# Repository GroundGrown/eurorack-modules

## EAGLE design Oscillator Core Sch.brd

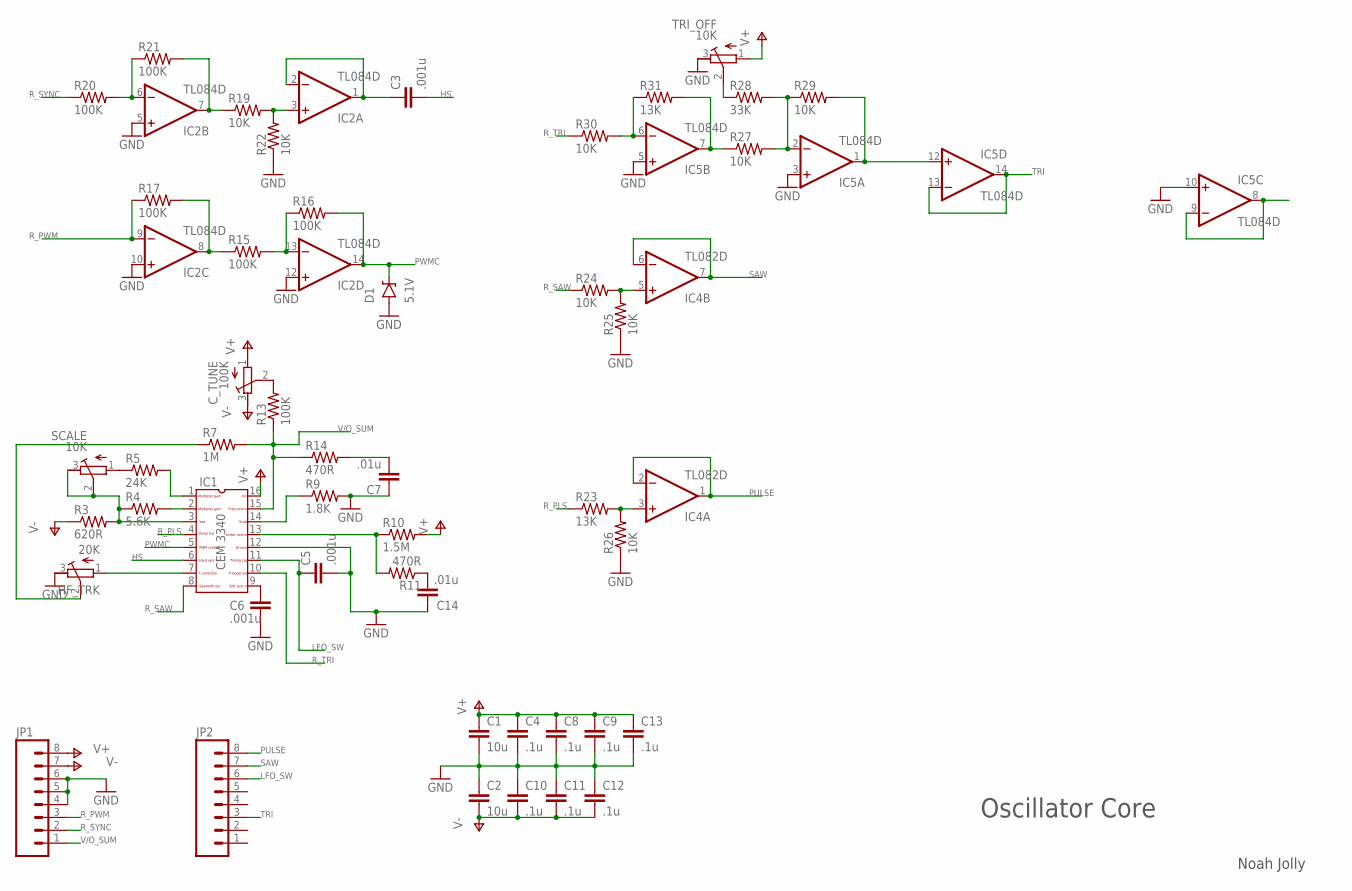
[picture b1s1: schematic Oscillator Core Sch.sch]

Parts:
C1, C2: 10u; 1206
C3, C6: .001u; 0805
C4, C8, C9, C10, C11, C12, C13: .1u; 0805
C5: .001u; CAP-PTH-5MM
C7, C14: .01u; 0805
C_TUNE: 100K; RTRIM3296Y
D1: 5.1V; SOD-123
HF_TRK: 20K; RTRIM3296Y
IC1: CEM3340; DIL16
IC2, IC5: TL084D; SO14
IC4: TL082D; SO08
JP1, JP2: M08; 1X08_ROUND
R3: 620R; 0805@1
R4: 5.6K; 0805@1
R5: 24K; 0805@1
R7: 1M; 0805@1
R9: 1.8K; 0805@1
R10: 1.5M; 0805@1
R11, R14: 470R; 0805@1
R13, R15, R16, R17, R20, R21: 100K; 0805@1
R19, R22, R24, R25, R26, R27, R29, R30: 10K; 0805@1
R23, R31: 13K; 0805@1
R28: 33K; 0805@1
SCALE: 10K; RTRIM3296Y
TRI_OFF: 10K; RTRIM3296Y

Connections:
GND: C1.2, C2.1, C4.2, C5.2, C6.2, C7.1, C8.2, C9.2, C10.1, C11.1, C12.1, C13.2, C14.1, D1.A, HF_TRK.3 (E), IC1.12, IC2.5 (+IN), IC2.10 (+IN), IC2.12 (+IN), IC5.3 (+IN), IC5.5 (+IN), IC5.10 (+IN), JP1.4, JP1.5, JP1.6, R9.2, R22.1, R25.1, R26.1, TRI_OFF.3 (E)
HS: C3.2, IC1.6
LFO_SW: C5.1, IC1.11, JP2.6
unnamed: R5.1, SCALE.1 (A)
unnamed: IC1.3, R3.2, R4.1, SCALE.2 (S), SCALE.3 (E)
unnamed: IC1.2, R4.2
unnamed: IC1.1, R5.2
unnamed: HF_TRK.2 (S), R7.1
unnamed: HF_TRK.1 (A), IC1.7
unnamed: C_TUNE.2 (S), R13.2
unnamed: IC1.14, R9.1
unnamed: IC1.13, R10.1, R11.2
unnamed: IC2.8 (OUT), R15.1, R17.2
unnamed: C6.1, IC1.9
unnamed: IC2.13 (-IN), R15.2, R16.1
unnamed: C7.2, R14.2
unnamed: IC4.5 (+IN), R24.2, R25.2
unnamed: IC5.8 (OUT), IC5.9 (-IN)
unnamed: C14.2, R11.1
unnamed: IC2.3 (+IN), R19.2, R22.2
unnamed: IC2.6 (-IN), R20.2, R21.1
unnamed: IC2.7 (OUT), R19.1, R21.2
unnamed: C3.1, IC2.1 (OUT), IC2.2 (-IN)
unnamed: IC4.3 (+IN), R23.2, R26.2
unnamed: IC5.6 (-IN), R30.2, R31.1
unnamed: IC5.7 (OUT), R27.1, R31.2
unnamed: IC5.2 (-IN), R27.2, R28.2, R29.1
unnamed: IC5.1 (OUT), IC5.12 (+IN), R29.2
unnamed: R28.1, TRI_OFF.2 (S)
PULSE: IC4.1 (OUT), IC4.2 (-IN), JP2.8
PWMC: D1.C, IC1.5, IC2.14 (OUT), R16.2
R_PLS: IC1.4, R23.1
R_PWM: IC2.9 (-IN), JP1.3, R17.1
R_SAW: IC1.8, R24.1
R_SYNC: JP1.2, R20.1
R_TRI: IC1.10, R30.1
SAW: IC4.6 (-IN), IC4.7 (OUT), JP2.7
TRI: IC5.13 (-IN), IC5.14 (OUT), JP2.3
V+: C1.1, C4.1, C8.1, C9.1, C13.1, C_TUNE.1 (A), IC1.16, IC2.4 (V+), IC4.8 (V+), IC5.4 (V+), JP1.8, R10.2, TRI_OFF.1 (A)
V-: C2.2, C10.2, C11.2, C12.2, C_TUNE.3 (E), IC2.11 (V-), IC4.4 (V-), IC5.11 (V-), JP1.7, R3.1
V/O_SUM: IC1.15, JP1.1, R7.2, R13.1, R14.1

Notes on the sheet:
Oscillator Core
Noah Jolly

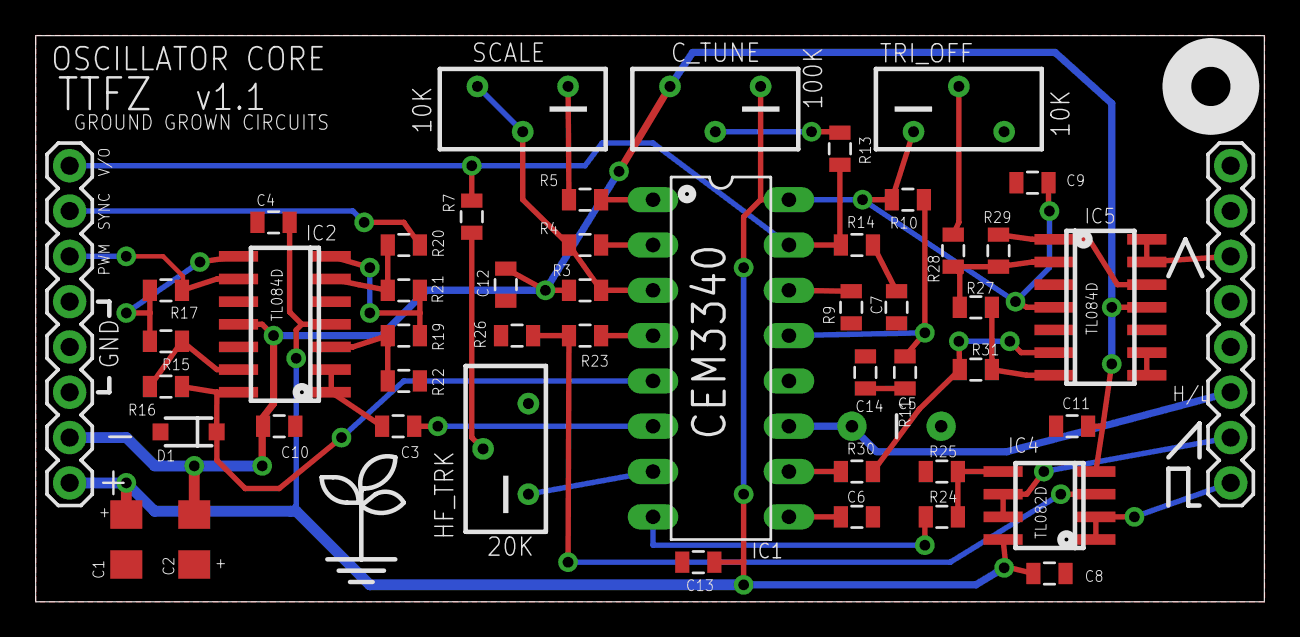
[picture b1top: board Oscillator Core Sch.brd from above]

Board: 2 copper layers, 68.9 x 31.7 mm, 50 parts (0 on the bottom side), 41 nets.

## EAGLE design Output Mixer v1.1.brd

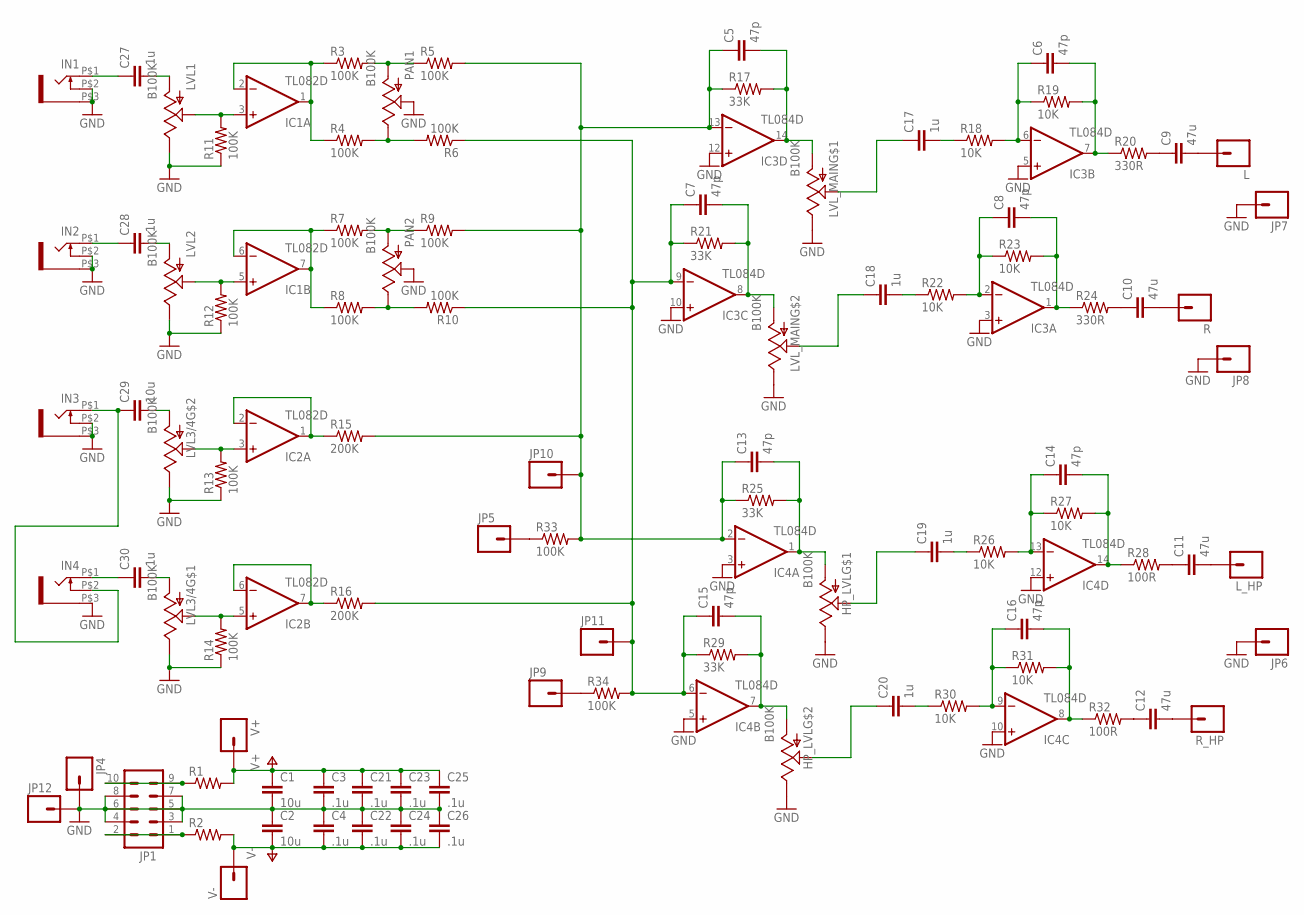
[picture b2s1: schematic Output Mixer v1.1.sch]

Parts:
C1, C2, C29: 10u; 1206
C3, C4, C21, C22, C23, C24, C25, C26: .1u; 0805
C5, C6, C7, C8, C13, C14, C15, C16: 47p; 0805
C9, C10, C11, C12: 47u; 1206
C17, C18, C19, C20: 1u; 0805
C27, C28, C30: .1u; 1206
HP_LVL: B100K; ALPS/ALPHA_POT_DUAL
IC1, IC2: TL082D; SO08
IC3, IC4: TL084D; SO14
IN1, IN2, IN3, IN4: WQP-PJ301M-12_JACK
JP1: M05X2PTH; AVR_ICSP
JP4, JP5, JP6, JP7, JP8, JP9, JP10, JP11, JP12: M01PTH; 1X01
L: M01PTH; 1X01
LVL1, LVL2: B100K; ALPS_POT
LVL3/4: B100K; ALPS/ALPHA_POT_DUAL
LVL_MAIN: B100K; ALPS/ALPHA_POT_DUAL
L_HP: M01PTH; 1X01
PAN1, PAN2: B100K; ALPS_POT
R: M01PTH; 1X01
R1, R2: RESISTOR0805-RES; 0805
R3, R4, R5, R6, R7, R8, R9, R10, R11, R12, R13, R14, R33, R34: 100K; 0805
R15, R16: 200K; 0805
R17, R21, R25, R29: 33K; 0805
R18, R19, R22, R23, R26, R27, R30, R31: 10K; 0805
R20, R24: 330R; 0805
R28, R32: 100R; 0805
R_HP: M01PTH; 1X01
V+: M01PTH; 1X01
V-: M01PTH; 1X01

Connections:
GND: C1.2, C2.1, C3.2, C4.1, C21.2, C22.1, C23.2, C24.1, C25.2, C26.1, HP_LVL.P$1 (E), HP_LVL.P$4 (E), IC3.3 (+IN), IC3.5 (+IN), IC3.10 (+IN), IC3.12 (+IN), IC4.3 (+IN), IC4.5 (+IN), IC4.10 (+IN), IC4.12 (+IN), IN1.P$2 (3), IN1.P$3 (1), IN2.P$2 (3), IN2.P$3 (1), IN3.P$2 (3), IN3.P$3 (1), IN4.P$3 (1), JP1.3, JP1.4, JP1.5, JP1.6, JP1.7, JP1.8, JP4.1, JP6.1, JP7.1, JP8.1, JP12.1, LVL1.P$1 (E), LVL2.P$1 (E), LVL3/4.P$1 (E), LVL3/4.P$4 (E), LVL_MAIN.P$1 (E), LVL_MAIN.P$4 (E), PAN1.P$2 (S), PAN2.P$2 (S), R11.1, R12.1, R13.1, R14.1
unnamed: JP1.9, JP1.10, R1.1
unnamed: JP1.1, JP1.2, R2.1
unnamed: JP5.1, R33.1
unnamed: JP9.1, R34.1
unnamed: C30.1, IN4.P$1 (2)
unnamed: C30.2, LVL3/4.P$3 (A)
unnamed: IC1.3 (+IN), LVL1.P$2 (S), R11.2
unnamed: IC1.5 (+IN), LVL2.P$2 (S), R12.2
unnamed: IC2.6 (-IN), IC2.7 (OUT), R16.1
unnamed: IC1.1 (OUT), IC1.2 (-IN), R3.1, R4.1
unnamed: IC1.6 (-IN), IC1.7 (OUT), R7.1, R8.1
unnamed: PAN1.P$3 (A), R3.2, R5.1
unnamed: PAN1.P$1 (E), R4.2, R6.2
unnamed: PAN2.P$3 (A), R7.2, R9.1
unnamed: PAN2.P$1 (E), R8.2, R10.2
unnamed: C29.1, IN3.P$1 (2), IN4.P$2 (3)
unnamed: IC2.3 (+IN), LVL3/4.P$5 (S), R13.2
unnamed: C9.1, R20.2
unnamed: IC2.5 (+IN), LVL3/4.P$2 (S), R14.2
unnamed: IC2.1 (OUT), IC2.2 (-IN), R15.1
unnamed: C10.1, R24.2
unnamed: C7.2, IC3.8 (OUT), LVL_MAIN.P$6 (A), R21.2
unnamed: C8.1, IC3.2 (-IN), R22.2, R23.1
unnamed: C8.2, IC3.1 (OUT), R23.2, R24.1
unnamed: C11.1, R28.2
unnamed: C5.2, IC3.14 (OUT), LVL_MAIN.P$3 (A), R17.2
unnamed: C6.1, IC3.6 (-IN), R18.2, R19.1
unnamed: C6.2, IC3.7 (OUT), R19.2, R20.1
unnamed: C12.1, R32.2
unnamed: C12.2, R_HP.1
unnamed: C11.2, L_HP.1
unnamed: C9.2, L.1
unnamed: C19.1, HP_LVL.P$2 (S)
unnamed: C19.2, R26.1
unnamed: C7.1, C15.1, IC3.9 (-IN), IC4.6 (-IN), JP11.1, R6.1, R10.1, R16.2, R21.1, R29.1, R34.2
unnamed: C15.2, HP_LVL.P$6 (A), IC4.7 (OUT), R29.2
unnamed: C16.1, IC4.9 (-IN), R30.2, R31.1
unnamed: C16.2, IC4.8 (OUT), R31.2, R32.1
unnamed: C5.1, C13.1, IC3.13 (-IN), IC4.2 (-IN), JP10.1, R5.2, R9.2, R15.2, R17.1, R25.1, R33.2
unnamed: C13.2, HP_LVL.P$3 (A), IC4.1 (OUT), R25.2
unnamed: C14.1, IC4.13 (-IN), R26.2, R27.1
unnamed: C14.2, IC4.14 (OUT), R27.2, R28.1
unnamed: C10.2, R.1
unnamed: C20.1, HP_LVL.P$5 (S)
unnamed: C20.2, R30.1
unnamed: C29.2, LVL3/4.P$6 (A)
unnamed: C18.1, LVL_MAIN.P$5 (S)
unnamed: C28.1, IN2.P$1 (2)
unnamed: C28.2, LVL2.P$3 (A)
unnamed: C27.1, IN1.P$1 (2)
unnamed: C27.2, LVL1.P$3 (A)
unnamed: C18.2, R22.1
unnamed: C17.1, LVL_MAIN.P$2 (S)
unnamed: C17.2, R18.1
V+: C1.1, C3.1, C21.1, C23.1, C25.1, IC1.8 (V+), IC2.8 (V+), IC3.4 (V+), IC4.4 (V+), R1.2, V+.1
V-: C2.2, C4.2, C22.2, C24.2, C26.2, IC1.4 (V-), IC2.4 (V-), IC3.11 (V-), IC4.11 (V-), R2.2, V-.1

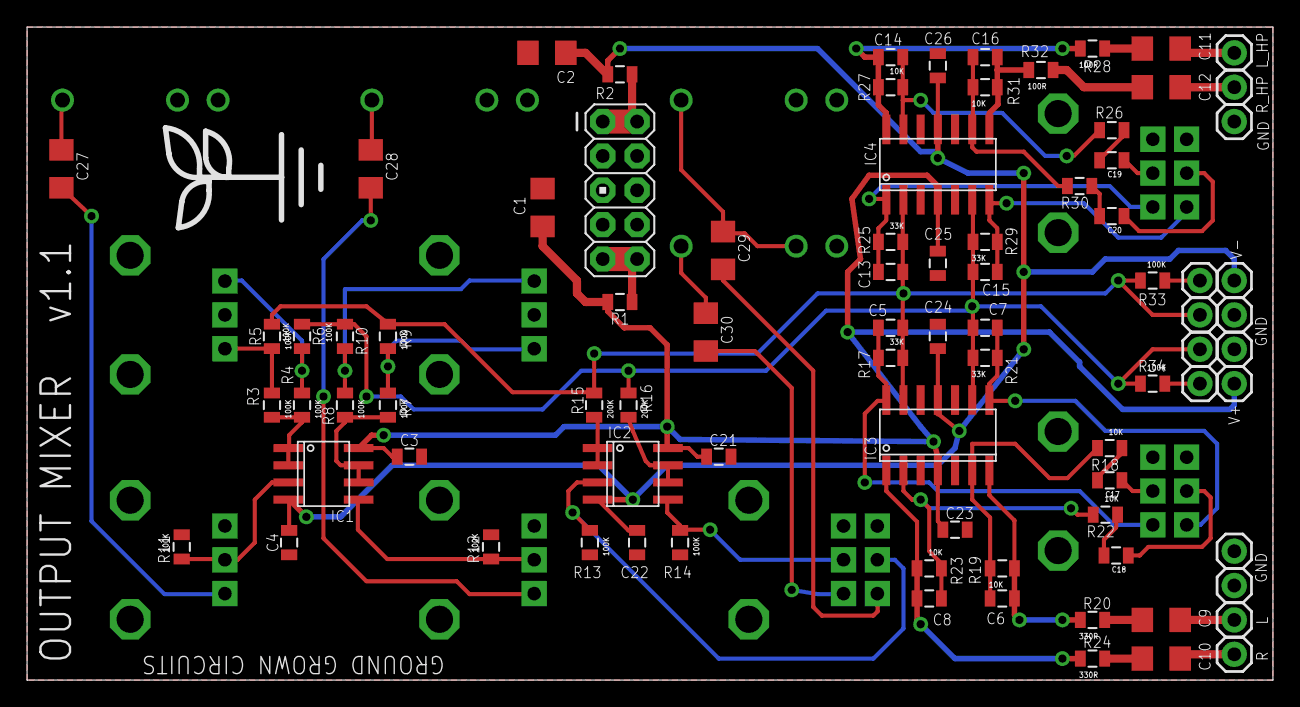
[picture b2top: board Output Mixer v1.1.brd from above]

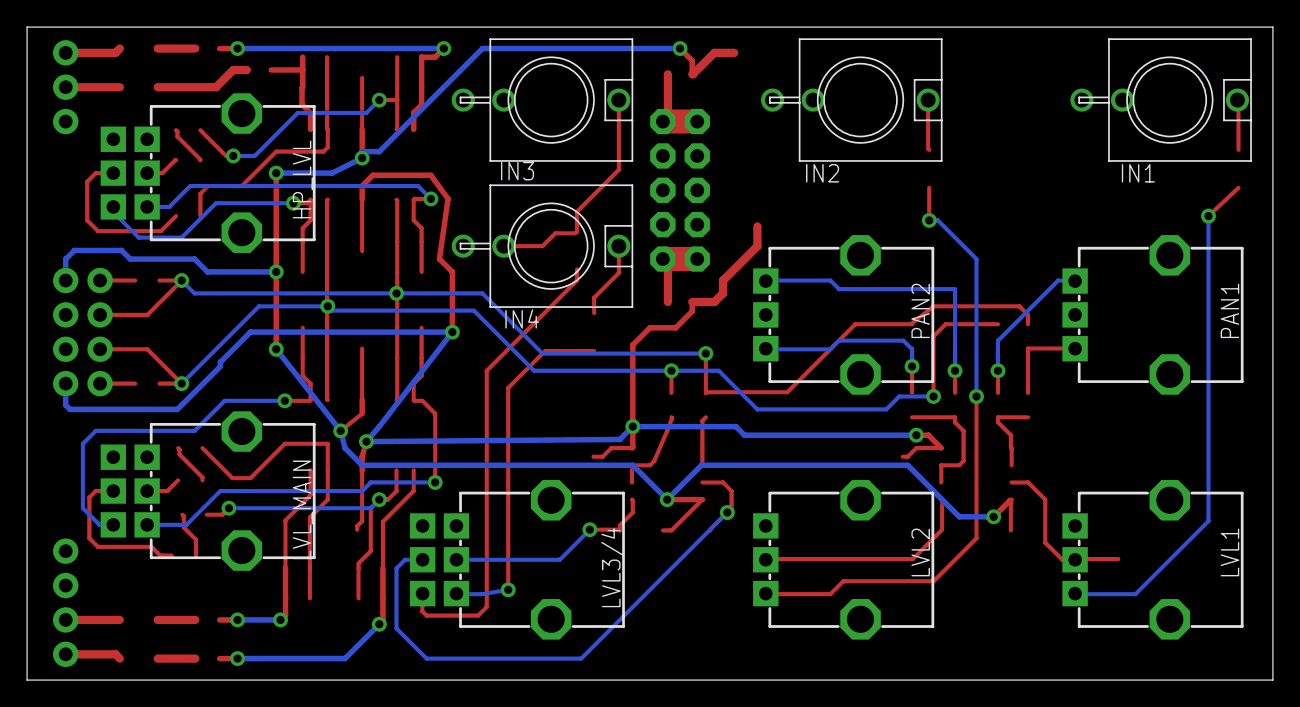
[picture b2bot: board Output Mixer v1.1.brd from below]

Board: 2 copper layers, 92.1 x 48.3 mm, 96 parts (11 on the bottom side), 57 nets.

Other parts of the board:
U$1: LOGO_MED

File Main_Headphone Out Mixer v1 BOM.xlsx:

2 | FERRITE BEAD | R1, R2
2 | 100R | R28, R32
2 | 330R | R20, R24
8 | 10K | R18, R19, R22, R23, R26, R27, R30, R31
4 | 33K | R17, R21, R25, R29
14 | 100K | R3, R4, R5, R6, R7, R8, R9, R10, R11, R12, R13, R14, R33, R34
2 | 200K | R15, R16
8 | 47p (0805) | C5, C6, C7, C8, C13, C14, C15, C16
8 | .1u (0805) | C3, C4, C21, C22, C23, C24, C25, C26
4 | .1u (1206) | C27, C28, C29, C30
2 | 10u (1206) | C1, C2
4 | 47u (1206) | C9, C10, C11, C12
2 | TL082 | IC1, IC2
2 | TL084 | IC3, IC4
1 | 2x5 pos male .1" Header | JP1
4 | B100K | LVL1, LVL2, PAN1, PAN2
3 | B100K DUAL GANG | LVL3/4, LVL_MAIN, HP_LVL
4 | WQP-PJ301M-12_JACK | IN1, IN2, IN3, IN4
2 | 1/4" MONO Jack | L_OUT, R_OUT | Switchcraft
1 | 1/4" STEREO Jack | HP_OUT | Switchcraft

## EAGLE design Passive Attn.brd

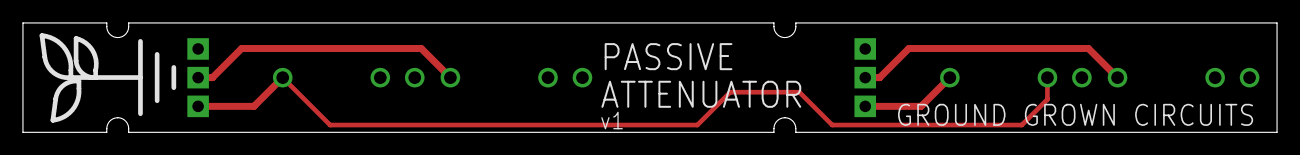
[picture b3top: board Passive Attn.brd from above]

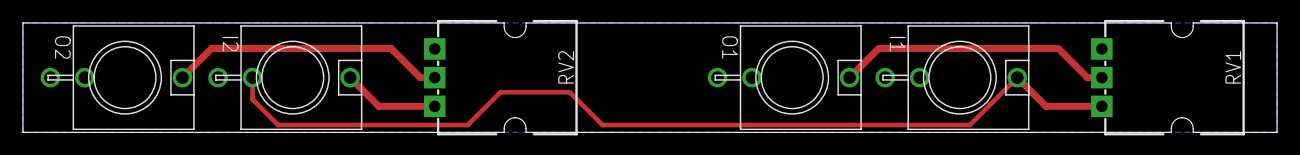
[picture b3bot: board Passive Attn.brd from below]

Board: 2 copper layers, 109.2 x 9.5 mm, 7 parts (6 on the bottom side), 5 nets.

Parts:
I1, I2: WQP-PJ301M-12_JACK
O1, O2: WQP-PJ301M-12_JACK
RV1, RV2: ALPS_POT_NO_CLIPS
U$1: LOGO_MED

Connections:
GND: I1.P$2, I1.P$3, I2.P$3, O1.P$3, O2.P$3, RV1.P$1, RV2.P$1
unnamed: O1.P$1, RV1.P$2
unnamed: I1.P$1, I2.P$2, RV1.P$3
unnamed: O2.P$1, RV2.P$2
unnamed: I2.P$1, RV2.P$3

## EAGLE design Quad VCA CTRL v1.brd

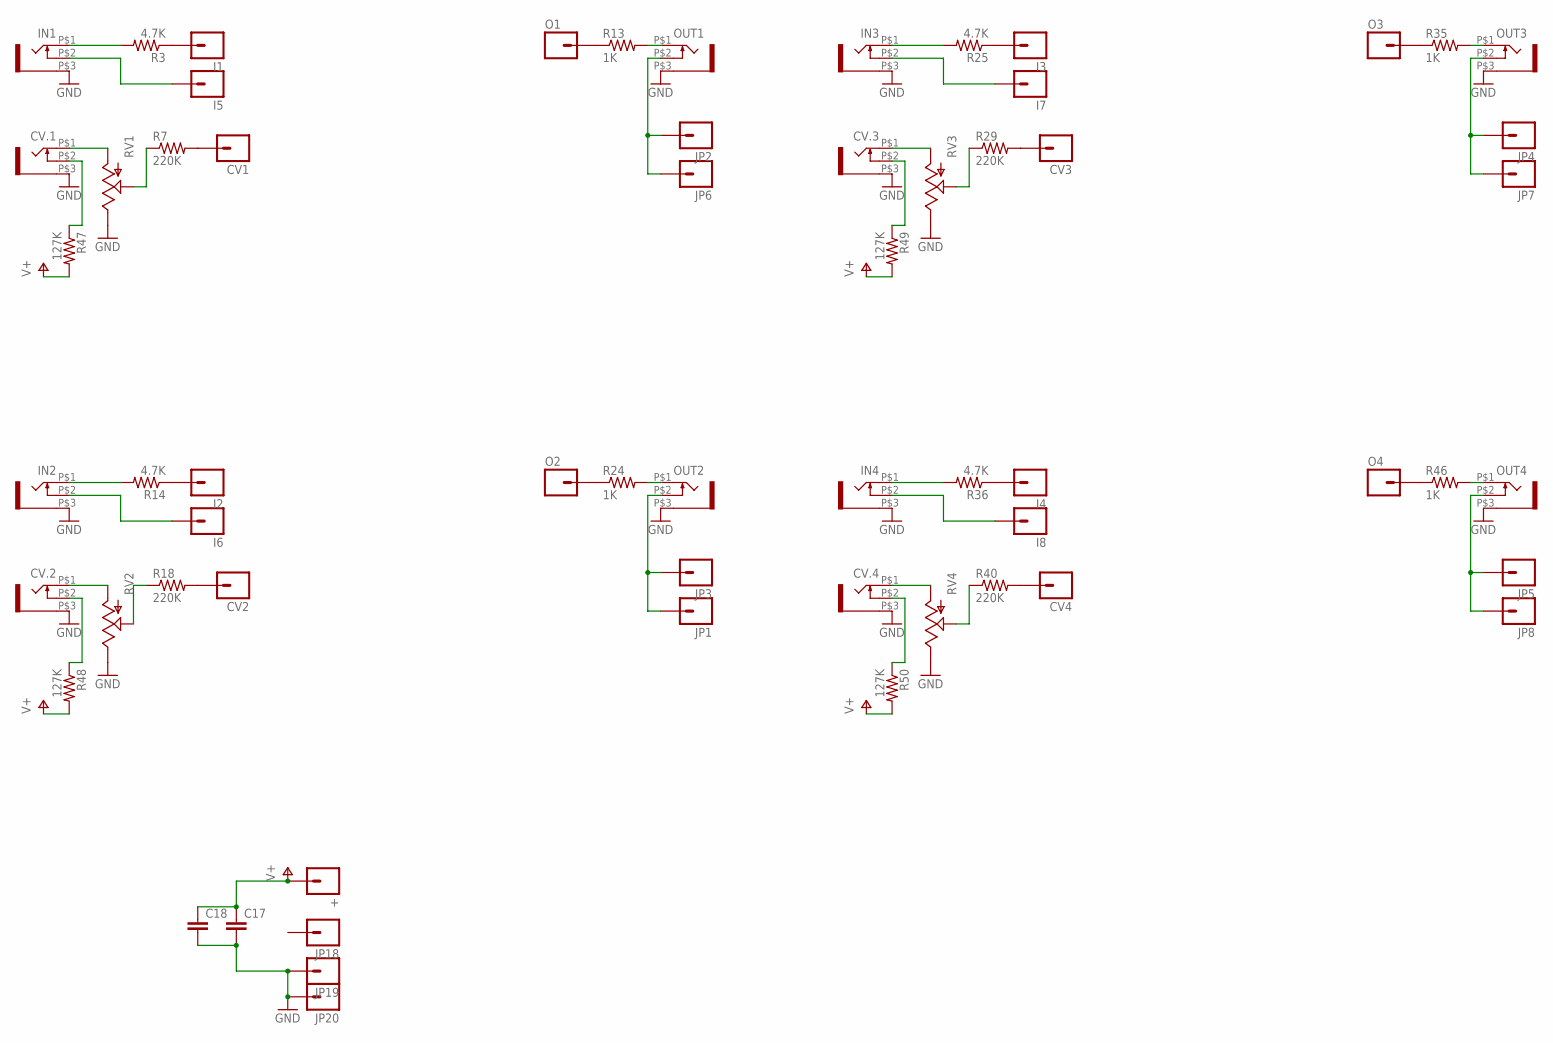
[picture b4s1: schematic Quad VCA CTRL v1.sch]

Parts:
+: M01PTH; 1X01
C17, C18: CAP0805; 0805
CV1, CV2, CV3, CV4: M01PTH; 1X01
CV.1, CV.2, CV.3, CV.4: WQP-PJ301M-12_JACK
I1, I2, I3, I4, I5, I6, I7, I8: M01PTH; 1X01
IN1, IN2, IN3, IN4: WQP-PJ301M-12_JACK
JP1, JP2, JP3, JP4, JP5, JP6, JP7, JP8, JP18, JP19, JP20: M01PTH; 1X01
O1, O2, O3, O4: M01PTH; 1X01
OUT1, OUT2, OUT3, OUT4: WQP-PJ301M-12_JACK
R3, R14, R25, R36: 4.7K; 0805
R7, R18, R29, R40: 220K; 0805
R13, R24, R35, R46: 1K; 0805
R47, R48, R49, R50: 127K; 0805
RV1, RV2, RV3, RV4: POT; ALPS_POT

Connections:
GND: C17.2, C18.2, CV.1.P$3 (1), CV.2.P$3 (1), CV.3.P$3 (1), CV.4.P$3 (1), IN1.P$3 (1), IN2.P$3 (1), IN3.P$3 (1), IN4.P$3 (1), JP19.1, JP20.1, OUT1.P$3 (1), OUT2.P$3 (1), OUT3.P$3 (1), OUT4.P$3 (1), RV1.P$1 (E), RV2.P$1 (E), RV3.P$1 (E), RV4.P$1 (E)
unnamed: CV.1.P$2 (3), R47.1
unnamed: I1.1, R3.1
unnamed: IN1.P$1 (2), R3.2
unnamed: CV1.1, R7.2
unnamed: O1.1, R13.1
unnamed: CV.2.P$1 (2), RV2.P$3 (A)
unnamed: CV.2.P$2 (3), R48.1
unnamed: CV.3.P$2 (3), R49.1
unnamed: CV.4.P$2 (3), R50.1
unnamed: JP2.1, JP6.1, OUT1.P$2 (3)
unnamed: IN2.P$1 (2), R14.2
unnamed: I2.1, R14.1
unnamed: O2.1, R24.1
unnamed: O3.1, R35.1
unnamed: O4.1, R46.1
unnamed: CV4.1, R40.2
unnamed: I4.1, R36.1
unnamed: CV3.1, R29.2
unnamed: R18.1, RV2.P$2 (S)
unnamed: CV.1.P$1 (2), RV1.P$3 (A)
unnamed: I3.1, R25.1
unnamed: CV2.1, R18.2
unnamed: I5.1, IN1.P$2 (3)
unnamed: I6.1, IN2.P$2 (3)
unnamed: OUT2.P$1 (2), R24.2
unnamed: IN3.P$1 (2), R25.2
unnamed: I7.1, IN3.P$2 (3)
unnamed: I8.1, IN4.P$2 (3)
unnamed: R7.1, RV1.P$2 (S)
unnamed: CV.3.P$1 (2), RV3.P$3 (A)
unnamed: R29.1, RV3.P$2 (S)
unnamed: CV.4.P$1 (2), RV4.P$3 (A)
unnamed: OUT1.P$1 (2), R13.2
unnamed: OUT3.P$1 (2), R35.2
unnamed: IN4.P$1 (2), R36.2
unnamed: R40.1, RV4.P$2 (S)
unnamed: JP1.1, JP3.1, OUT2.P$2 (3)
unnamed: OUT4.P$1 (2), R46.2
unnamed: JP4.1, JP7.1, OUT3.P$2 (3)
unnamed: JP5.1, JP8.1, OUT4.P$2 (3)
V+: +.1, C17.1, C18.1, R47.2, R48.2, R49.2, R50.2

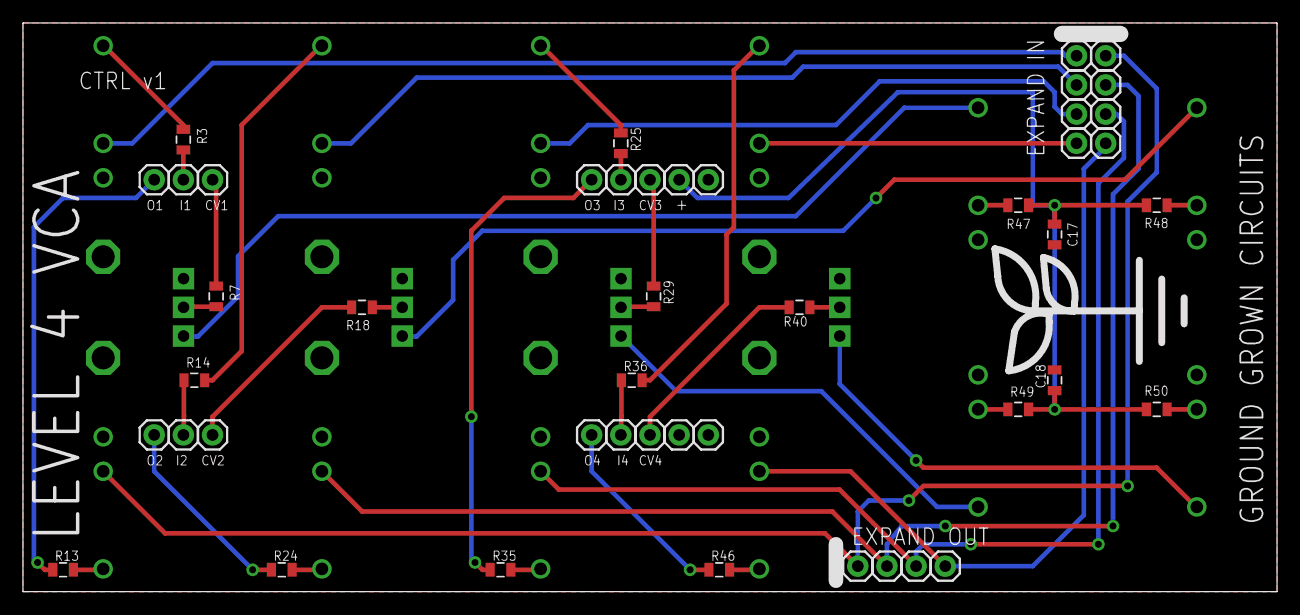
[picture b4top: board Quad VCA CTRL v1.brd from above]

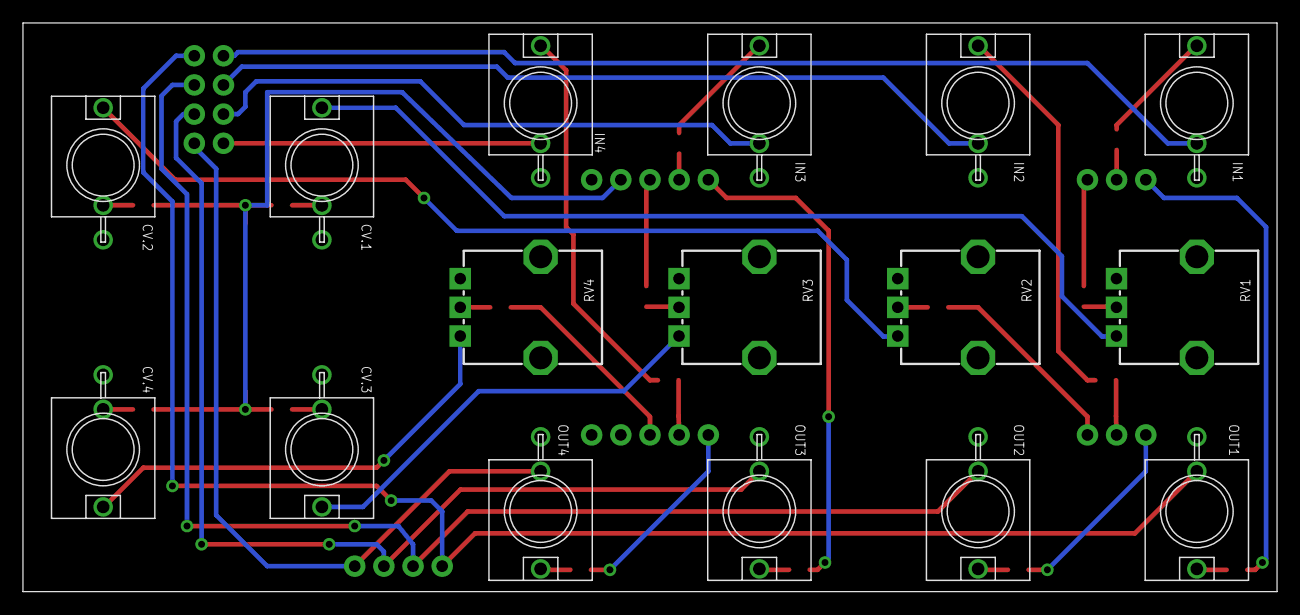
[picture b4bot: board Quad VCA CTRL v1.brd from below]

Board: 2 copper layers, 109.2 x 49.5 mm, 63 parts (16 on the bottom side), 42 nets.

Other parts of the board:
U$1: LOGO_LARGE

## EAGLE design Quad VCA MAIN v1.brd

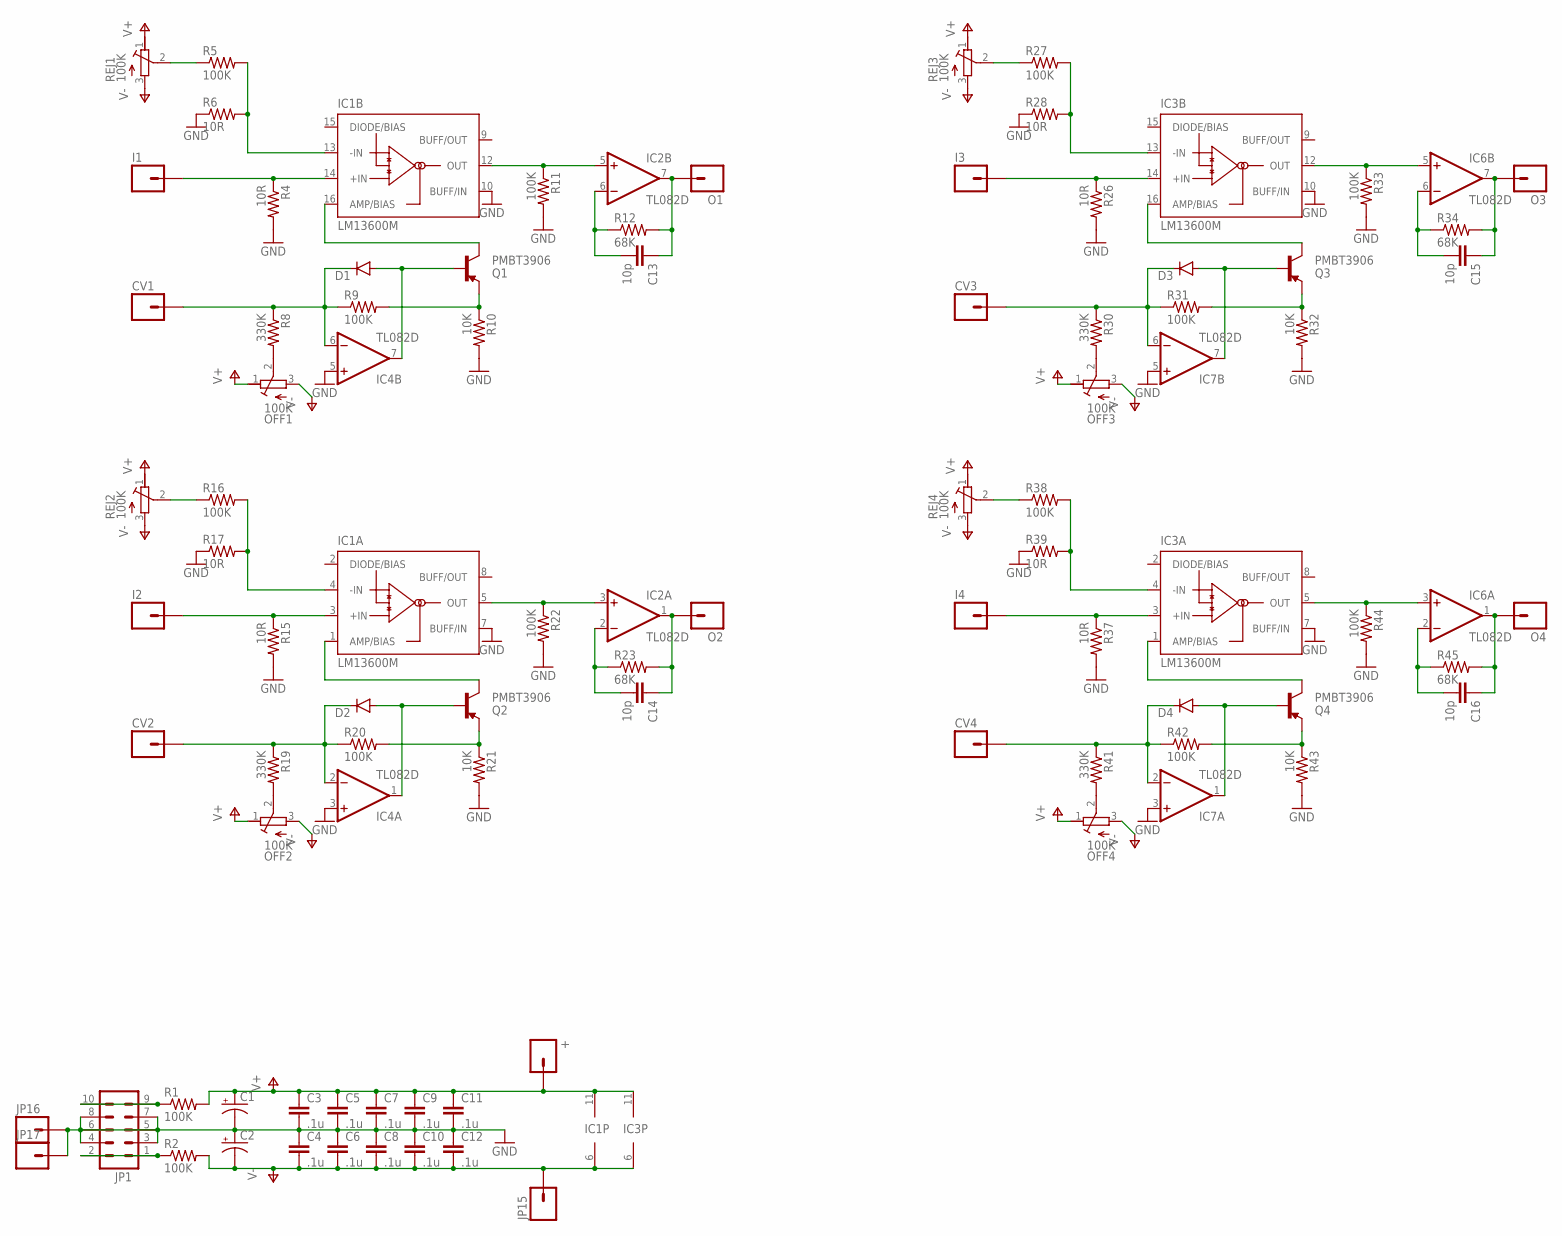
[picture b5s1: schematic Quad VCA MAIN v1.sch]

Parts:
+: M01PTH; 1X01
C1, C2: CAP_POLPTH2; CPOL-RADIAL-10UF-25V
C3, C4, C5, C6, C7, C8, C9, C10, C11, C12: .1u; 0805
C13, C14, C15, C16: 10p; 0805
CV1, CV2, CV3, CV4: M01PTH; 1X01
D1, D2, D3, D4: DIODESOD123; SOD-123
I1, I2, I3, I4: M01PTH; 1X01
IC1, IC3: LM13600M; SO16
IC2, IC4, IC6, IC7: TL082D; SO08
JP1: M05X2PTH; AVR_ICSP
JP15, JP16, JP17: M01PTH; 1X01
O1, O2, O3, O4: M01PTH; 1X01
OFF1, OFF2, OFF3, OFF4: 100K; RTRIM3314G
Q1, Q2, Q3, Q4: PMBT3906; SOT23-3
R1, R2, R5, R9, R11, R16, R20, R22, R27, R31, R33, R38, R42, R44: 100K; 0805
R4, R6, R15, R17, R26, R28, R37, R39: 10R; 0805
R8, R19, R30, R41: 330K; 0805
R10, R21, R32, R43: 10K; 0805
R12, R23, R34, R45: 68K; 0805
REJ1, REJ2, REJ3, REJ4: 100K; RTRIM3314G

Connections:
GND: C1.2 (-), C2.1 (+), C3.2, C4.1, C5.2, C6.1, C7.2, C8.1, C9.2, C10.1, C11.2, C12.1, IC1.7 (BUFF/IN), IC1.10 (BUFF/IN), IC3.7 (BUFF/IN), IC3.10 (BUFF/IN), IC4.3 (+IN), IC4.5 (+IN), IC7.3 (+IN), IC7.5 (+IN), JP1.3, JP1.4, JP1.5, JP1.6, JP1.7, JP1.8, JP16.1, JP17.1, R4.2, R6.1, R10.2, R11.2, R15.2, R17.1, R21.2, R22.2, R26.2, R28.1, R32.2, R33.2, R37.2, R39.1, R43.2, R44.2
unnamed: JP1.9, JP1.10, R1.1
unnamed: I1.1, IC1.14 (+IN), R4.1
unnamed: JP1.1, JP1.2, R2.1
unnamed: I2.1, IC1.3 (+IN), R15.1
unnamed: R16.1, REJ2.2 (S)
unnamed: IC1.4 (-IN), R16.2, R17.2
unnamed: OFF2.2 (S), R19.2
unnamed: CV2.1, D2.C, IC4.2 (-IN), R19.1, R20.1
unnamed: Q2.2 (E), R20.2, R21.1
unnamed: D2.A, IC4.1 (OUT), Q2.1 (B)
unnamed: IC1.1 (AMP/BIAS), Q2.3 (C)
unnamed: IC1.5 (OUT), IC2.3 (+IN), R22.1
unnamed: C14.2, IC2.2 (-IN), R23.1
unnamed: C14.1, IC2.1 (OUT), O2.1, R23.2
unnamed: I3.1, IC3.14 (+IN), R26.1
unnamed: R27.1, REJ3.2 (S)
unnamed: IC3.13 (-IN), R27.2, R28.2
unnamed: OFF3.2 (S), R30.2
unnamed: CV3.1, D3.C, IC7.6 (-IN), R30.1, R31.1
unnamed: Q3.2 (E), R31.2, R32.1
unnamed: D3.A, IC7.7 (OUT), Q3.1 (B)
unnamed: IC3.16 (AMP/BIAS), Q3.3 (C)
unnamed: IC3.12 (OUT), IC6.5 (+IN), R33.1
unnamed: C15.2, IC6.6 (-IN), R34.1
unnamed: R5.1, REJ1.2 (S)
unnamed: IC1.13 (-IN), R5.2, R6.2
unnamed: OFF1.2 (S), R8.2
unnamed: CV1.1, D1.C, IC4.6 (-IN), R8.1, R9.1
unnamed: Q1.2 (E), R9.2, R10.1
unnamed: D1.A, IC4.7 (OUT), Q1.1 (B)
unnamed: IC1.16 (AMP/BIAS), Q1.3 (C)
unnamed: IC1.12 (OUT), IC2.5 (+IN), R11.1
unnamed: C13.2, IC2.6 (-IN), R12.1
unnamed: C13.1, IC2.7 (OUT), O1.1, R12.2
unnamed: C15.1, IC6.7 (OUT), O3.1, R34.2
unnamed: I4.1, IC3.3 (+IN), R37.1
unnamed: R38.1, REJ4.2 (S)
unnamed: IC3.4 (-IN), R38.2, R39.2
unnamed: OFF4.2 (S), R41.2
unnamed: CV4.1, D4.C, IC7.2 (-IN), R41.1, R42.1
unnamed: Q4.2 (E), R42.2, R43.1
unnamed: D4.A, IC7.1 (OUT), Q4.1 (B)
unnamed: IC3.1 (AMP/BIAS), Q4.3 (C)
unnamed: IC3.5 (OUT), IC6.3 (+IN), R44.1
unnamed: C16.2, IC6.2 (-IN), R45.1
unnamed: C16.1, IC6.1 (OUT), O4.1, R45.2
V+: +.1, C1.1 (+), C3.1, C5.1, C7.1, C9.1, C11.1, IC1.11 (V+), IC2.8 (V+), IC3.11 (V+), IC4.8 (V+), IC6.8 (V+), IC7.8 (V+), OFF1.1 (E), OFF2.1 (E), OFF3.1 (E), OFF4.1 (E), R1.2, REJ1.1 (E), REJ2.1 (E), REJ3.1 (E), REJ4.1 (E)
V-: C2.2 (-), C4.2, C6.2, C8.2, C10.2, C12.2, IC1.6 (V-), IC2.4 (V-), IC3.6 (V-), IC4.4 (V-), IC6.4 (V-), IC7.4 (V-), JP15.1, OFF1.3 (A), OFF2.3 (A), OFF3.3 (A), OFF4.3 (A), R2.2, REJ1.3 (A), REJ2.3 (A), REJ3.3 (A), REJ4.3 (A)

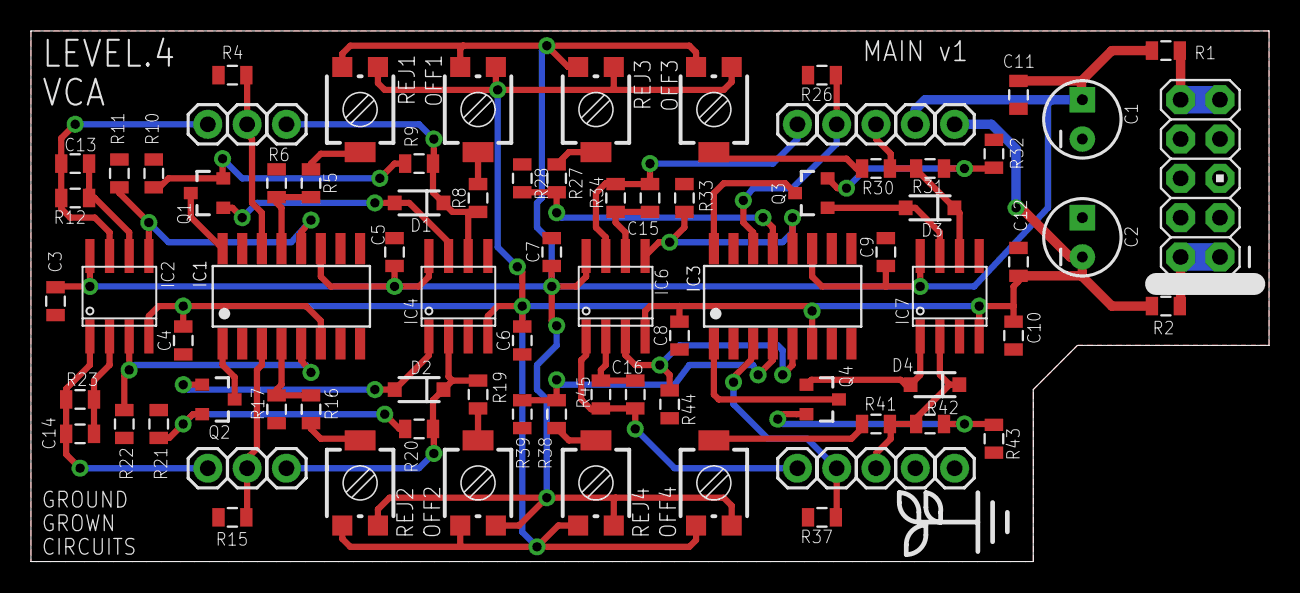
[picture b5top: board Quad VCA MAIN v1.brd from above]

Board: 2 copper layers, 80.0 x 34.3 mm, 90 parts (0 on the bottom side), 49 nets.

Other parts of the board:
U$1: LOGO_SMALL

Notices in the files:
parts and their libraries:
SparkFun-Capacitors: Licensing: Creative Commons ShareAlike 4.0 International - https://creativecommons.org/licenses/by-sa/4.0
